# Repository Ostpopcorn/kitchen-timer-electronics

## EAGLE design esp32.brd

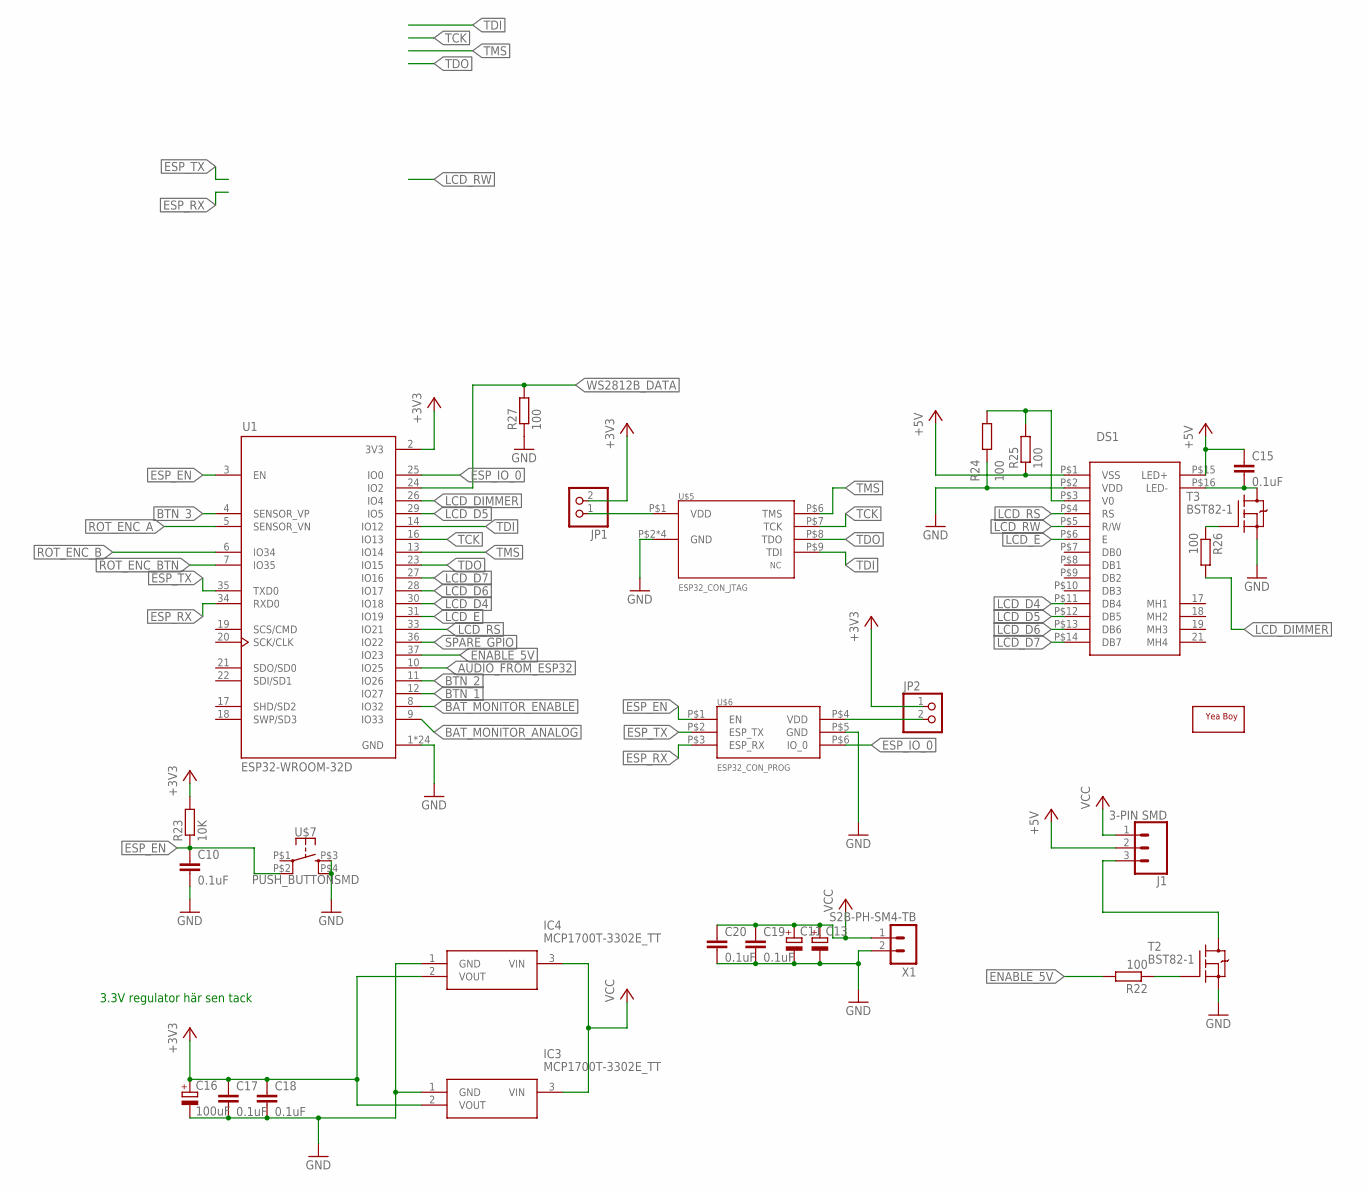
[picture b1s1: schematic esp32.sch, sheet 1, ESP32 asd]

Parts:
C10, C15, C17, C18, C19, C20: 0.1uF; C0603
C11: CPOL-EU153CLV-0605; 153CLV-0605
C13: CPOL-EU153CLV-0505; 153CLV-0505
C16: 100uF; 153CLV-0605
DS1: NHD-0216XZ-FSW-GBWSMT; NHD0216XZFSWGBW_SMT
IC3, IC4: MCP1700T-3302E_TT; SOT95P237X112-3N
J1: 3-PIN SMD; JST-3-SMD
JP1, JP2: PINHD-1X2; 1X02
R22, R24, R25, R26, R27: 100; R0603
R23: 10K; R0603
T2, T3: BST82-1; SOT23
U1: ESP32-WROOM-32D; MODULE_ESP32-WROOM-32D
U$5: ESP32_CON_JTAG; DC3_10P_0.05
U$6: ESP32_CON_PROG; DC3_6P_0.05
U$7: PUSH_BUTTONSMD; TACTILE_SWITCH_PTH_6.0MM_SMD
U$8: TOUCHMARK
X1: S2B-PH-SM4-TB

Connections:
+3V3: C16.+, C17.1, C18.1, IC3.2 (VOUT), IC4.2 (VOUT), JP1.2, JP2.1, R23.2, U1.2 (3V3); also elsewhere on the board
+5V: C15.1, DS1.P$1 (VSS), DS1.P$15 (LED+), J1.2, R25.1; also elsewhere on the board
AUDIO_FROM_ESP32: U1.10 (IO25); also elsewhere on the board
BAT_MONITOR_ANALOG: U1.9 (IO33); also elsewhere on the board
BAT_MONITOR_ENABLE: U1.8 (IO32); also elsewhere on the board
BTN_1: U1.12 (IO27); also elsewhere on the board
BTN_2: U1.11 (IO26); also elsewhere on the board
BTN_3: U1.4 (SENSOR_VP); also elsewhere on the board
ENABLE_5V: R22.2, U1.37 (IO23)
ESP_EN: C10.1, R23.1, U1.3 (EN), U$6.P$1 (EN), U$7.P$2 (2)
ESP_IO_0: U1.25 (IO0), U$6.P$6 (IO_0)
ESP_RX: U1.34 (RXD0), U$6.P$3 (ESP_RX)
ESP_TX: U1.35 (TXD0), U$6.P$2 (ESP_TX)
GND: C10.2, C11.-, C13.-, C16.-, C17.2, C18.2, C19.2, C20.2, DS1.P$2 (VDD), IC3.1 (GND), IC4.1 (GND), R24.1, R27.1, T2.2 (S), T3.2 (S), U1.1 (GND), U1.15 (GND), U1.38 (GND), U1.39_1 (GND), U1.39_2 (GND), U1.39_3 (GND), U1.39_4 (GND), U1.39_5 (GND), U1.39_6 (GND), U1.39_7 (GND), U1.39_8 (GND), U1.39_9 (GND), U1.39_10 (GND), U1.39_11 (GND), U1.39_12 (GND), U1.39_13 (GND), U1.39_14 (GND), U1.39_15 (GND), U1.39_16 (GND), U1.39_17 (GND), U1.39_18 (GND), U1.39_19 (GND), U1.39_20 (GND), U1.39_21 (GND), U$5.P$2 (GND), U$5.P$3 (GND), U$5.P$4 (GND), U$5.P$5 (GND), U$6.P$5 (GND), U$7.P$3 (3), U$7.P$4 (4), X1.2; also elsewhere on the board
LCD_D4: DS1.P$11 (DB4), U1.30 (IO18)
LCD_D5: DS1.P$12 (DB5), U1.29 (IO5)
LCD_D6: DS1.P$13 (DB6), U1.28 (IO17)
LCD_D7: DS1.P$14 (DB7), U1.27 (IO16)
LCD_DIMMER: R26.2, U1.26 (IO4)
LCD_E: DS1.P$6 (E), U1.31 (IO19)
LCD_RS: DS1.P$4 (RS), U1.33 (IO21)
LCD_RW: DS1.P$5 (R/W)
unnamed: R22.1, T2.1 (G)
unnamed: J1.3, T2.3 (D)
unnamed: R26.1, T3.1 (G)
unnamed: DS1.P$3 (V0), R24.2, R25.2
unnamed: C15.2, DS1.P$16 (LED-), T3.3 (D)
unnamed: JP2.2, U$6.P$4 (VDD)
unnamed: JP1.1, U$5.P$1 (VDD)
ROT_ENC_A: U1.5 (SENSOR_VN); also elsewhere on the board
ROT_ENC_B: U1.6 (IO34); also elsewhere on the board
ROT_ENC_BTN: U1.7 (IO35); also elsewhere on the board
SPARE_GPIO: U1.36 (IO22)
TCK: U1.16 (IO13), U$5.P$7 (TCK)
TDI: U1.14 (IO12), U$5.P$9 (TDI)
TDO: U1.23 (IO15), U$5.P$8 (TDO)
TMS: U1.13 (IO14), U$5.P$6 (TMS)
VCC: C11.+, C13.+, C19.1, C20.1, IC3.3 (VIN), IC4.3 (VIN), J1.1, X1.1; also elsewhere on the board
WS2812B_DATA: R27.2, U1.24 (IO2); also elsewhere on the board

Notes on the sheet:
3.3V regulator här sen tack

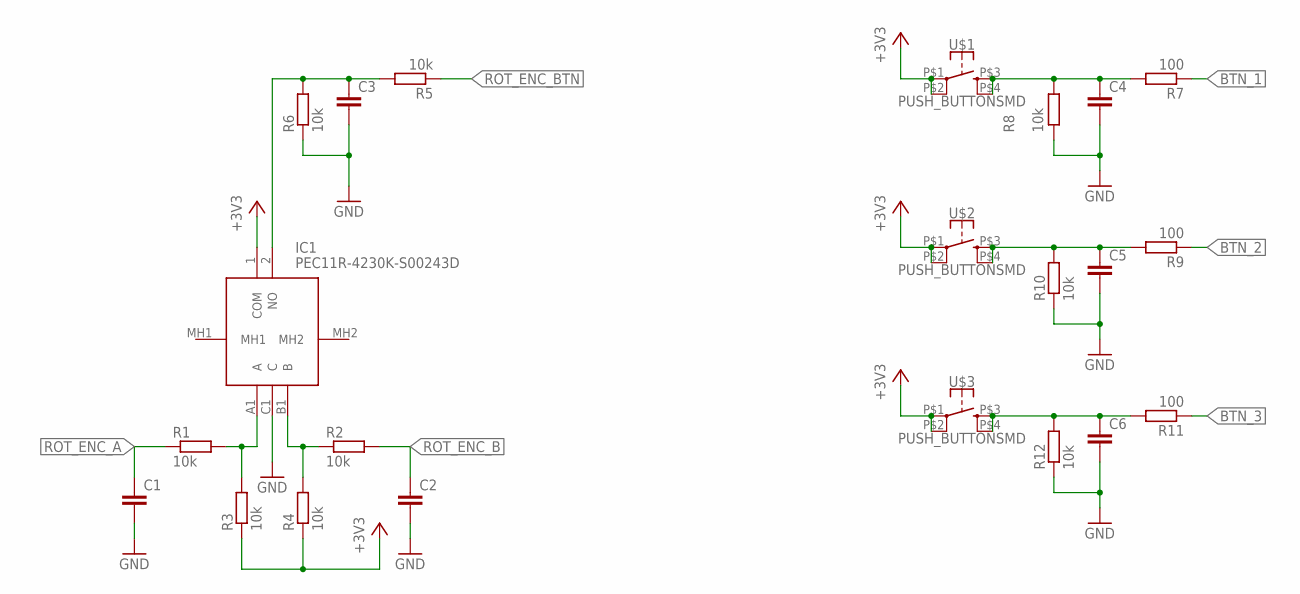
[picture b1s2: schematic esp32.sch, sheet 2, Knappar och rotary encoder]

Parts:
C1, C2, C3, C4, C5, C6: C-EUC0603; C0603
IC1: PEC11R-4230K-S00243D; PEC11R4230KS0024
R1, R2, R3, R4, R5, R6, R8, R10, R12: 10k; R0603
R7, R9, R11: 100; R0603
U$1, U$2, U$3: PUSH_BUTTONSMD; TACTILE_SWITCH_PTH_6.0MM_SMD

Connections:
+3V3: IC1.1 (COM), R3.1, R4.1, U$1.P$1 (1), U$1.P$2 (2), U$2.P$1 (1), U$2.P$2 (2), U$3.P$1 (1), U$3.P$2 (2); also elsewhere on the board
BTN_1: R7.1; also elsewhere on the board
BTN_2: R9.1; also elsewhere on the board
BTN_3: R11.1; also elsewhere on the board
GND: C1.2, C2.2, C3.2, C4.2, C5.2, C6.2, IC1.C1 (C), R6.1, R8.1, R10.1, R12.1; also elsewhere on the board
unnamed: IC1.A1 (A), R1.2, R3.2
unnamed: IC1.B1 (B), R2.1, R4.2
unnamed: C4.1, R7.2, R8.2, U$1.P$3 (3), U$1.P$4 (4)
unnamed: C5.1, R9.2, R10.2, U$2.P$3 (3), U$2.P$4 (4)
unnamed: C6.1, R11.2, R12.2, U$3.P$3 (3), U$3.P$4 (4)
unnamed: C3.1, IC1.2 (NO), R5.2, R6.2
ROT_ENC_A: C1.1, R1.1; also elsewhere on the board
ROT_ENC_B: C2.1, R2.2; also elsewhere on the board
ROT_ENC_BTN: R5.1; also elsewhere on the board

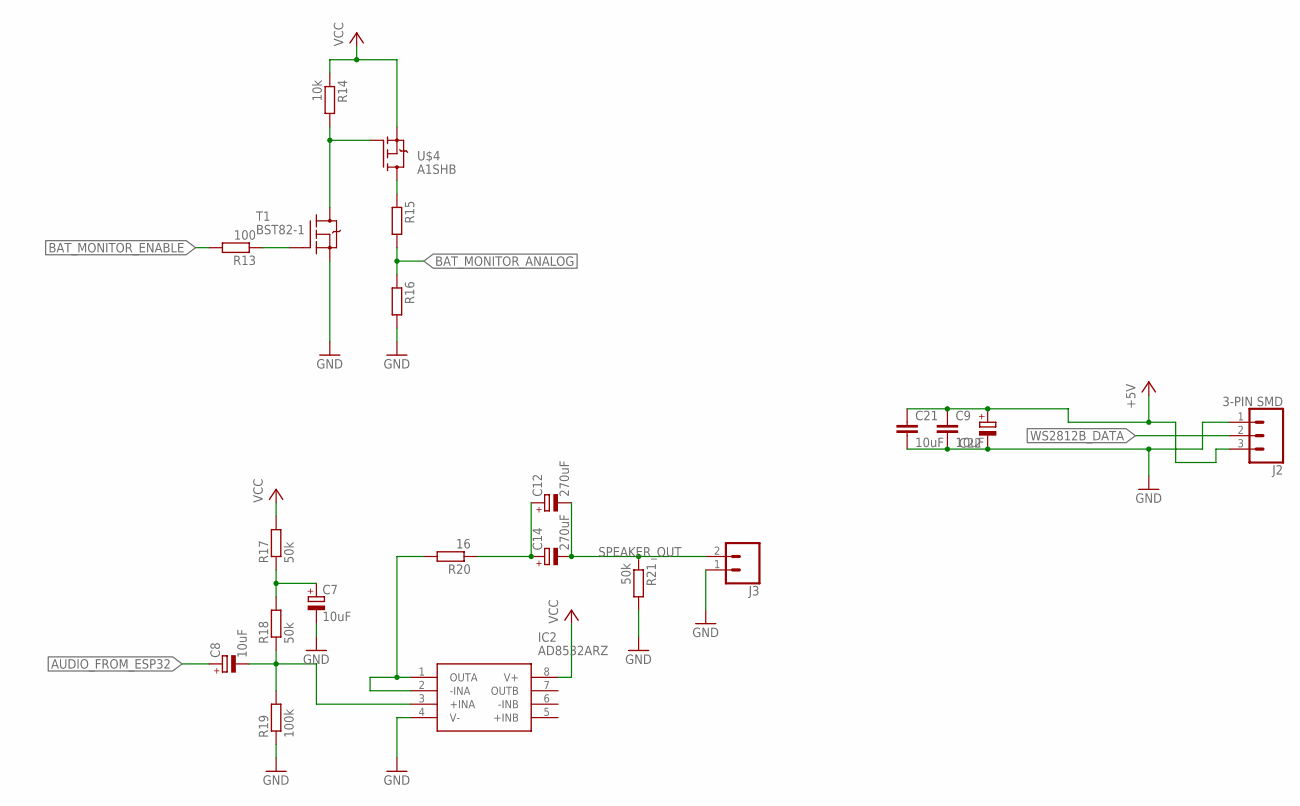
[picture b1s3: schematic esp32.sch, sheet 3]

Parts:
C7, C8: 10uF; 153CLV-0505
C9, C21: 10uF; C0603
C12, C14: 270uF; 153CLV-0605
C22: CPOL-EU153CLV-0605; 153CLV-0605
IC2: AD8532ARZ; SOIC127P600X175-8N
J2: 3-PIN SMD; JST-3-SMD
J3: CONN_02-JST-2MM-SMT; JST-2-SMD
R13: 100; R0603
R14: 10k; R0603
R15, R16: R-EU_R0603; R0603
R17, R18, R21: 50k; R0603
R19: 100k; R0603
R20: 16; R0603
T1: BST82-1; SOT23
U$4: A1SHB; SOT23

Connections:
+5V: C9.1, C21.1, C22.+, J2.3; also elsewhere on the board
AUDIO_FROM_ESP32: C8.+; also elsewhere on the board
BAT_MONITOR_ANALOG: R15.2, R16.1; also elsewhere on the board
BAT_MONITOR_ENABLE: R13.2; also elsewhere on the board
GND: C7.-, C9.2, C21.2, C22.-, IC2.4 (V-), J2.1, J3.1 (2), R16.2, R19.1, R21.2, T1.2 (S); also elsewhere on the board
unnamed: C8.-, IC2.3 (+INA), R18.1, R19.2
unnamed: R15.1, U$4.3 (D)
unnamed: R14.2, T1.3 (D), U$4.1 (G)
unnamed: C7.+, R17.1, R18.2
unnamed: IC2.1 (OUTA), IC2.2 (-INA), R20.2
unnamed: R13.1, T1.1 (G)
unnamed: C12.+, C14.+, R20.1
SPEAKER_OUT: C12.-, C14.-, J3.2 (1), R21.1
VCC: IC2.8 (V+), R14.1, R17.2, U$4.2 (S); also elsewhere on the board
WS2812B_DATA: J2.2; also elsewhere on the board

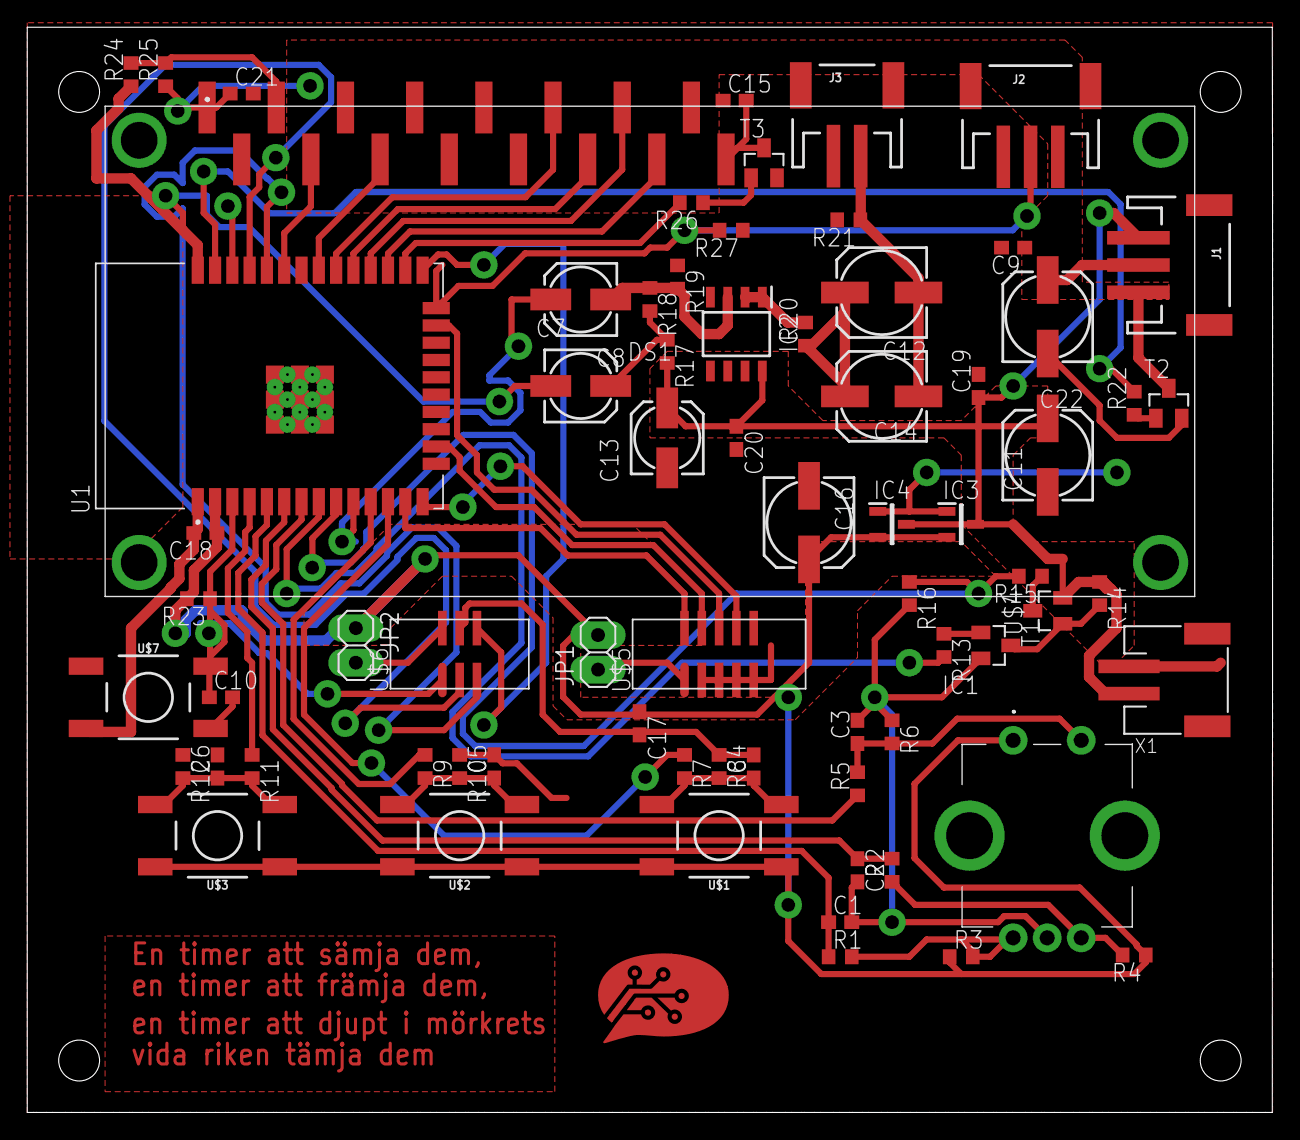
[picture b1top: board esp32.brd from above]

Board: 2 copper layers, 91.4 x 79.7 mm, 72 parts (0 on the bottom side), 51 nets.

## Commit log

2020-11-13 Created almost empty EAGLE project.
2020-11-14 Stora dela av schematic är klart. Saknar fortfarande vissa viktiga delar, men då måste jag passera admittansen först.
2020-11-16 Lite grovt upplägg av vissa komponenter på kortet.
2020-11-16 Bra upplägg på kortet men saknar fortfarande 3.3V regulator.
2020-11-16 La till hål i ytterkanterna.
2020-11-16 Kom på att man ska lägga till en reset-knapp... Men saknar fortfarande massa kondingar och sen 3.3V regulator.
2020-11-19 La till kondingar och kopplade alla signaler, precis lagom många GPIO pinnar på ESP32an typ bara 2 över!
2020-11-19 Fixade så att texten har orphans i fyllkomandot, såg konstigt ut annars.
2020-11-19 Added dimmer for lcd and starting redouting to 18mil
2020-11-19 Alla diken är nu 18mil. Nästa är att koppla de sista signalerna till esp32
2020-11-19 Kopplade alla signaler, ska göra om footprint för LCD och sen sätta på 3.3V regulator och sen borde den vara komplett!
2020-11-22 Delade upp i lite olika plan. Rätta footprints för kondingar och 3.3V regulator.
2020-11-22 En lite fix till. :)
2020-11-25 Delad upp jordplanet till flera beroende på signal, hört att det ska vara bra att ta bort loopar i jorden.
2020-11-29 Nya upplägget fungera bra, kanske till och med mindre vior än innan, får in mer på mindre plats också. Kommit kanske 70% nu.
2020-11-30 All är routat, behövs dock nya avtryck för JST och skämen.
2020-12-01 Tror fan att den är färdig nu, allt som ska bli SMT är SMT nu och rätt pinnar för rätt sak förhoppningsvis.

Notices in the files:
parts and their libraries:
SparkFun-Connectors: Licensing: Creative Commons ShareAlike 4.0 International - https://creativecommons.org/licenses/by-sa/4.0
